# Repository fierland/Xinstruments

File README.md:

NOT DONE YET

This is the code library for my Cessna 172 Cockpit project. Just starting will add the print layouts, sketchuo and other files later. I'm just stating :-)

DONE:
 - design small instruments
 - lasercutter files small instruments
 - electronics small instruments
 - generic code for instruments
 
TODO:
 - big instruments
 - communication (CAN Areospace) layer
 - central controler
 
---

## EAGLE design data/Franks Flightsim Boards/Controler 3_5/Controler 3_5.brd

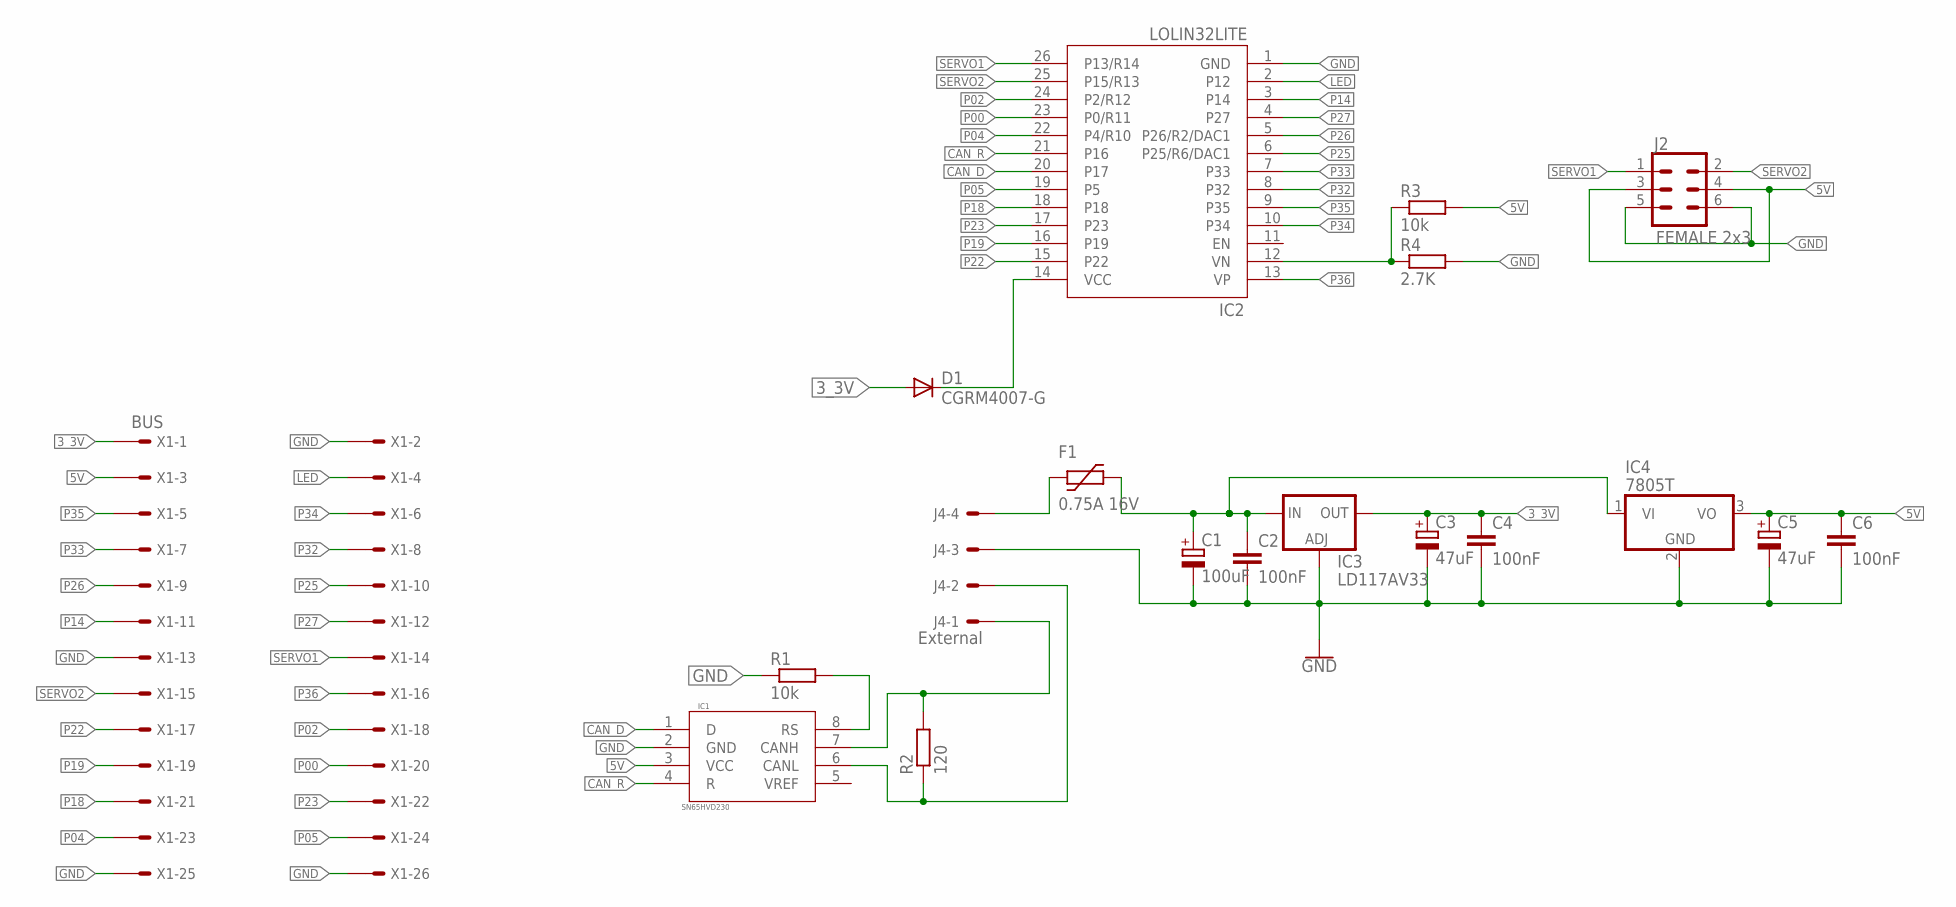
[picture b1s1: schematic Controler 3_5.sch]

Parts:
C1: 100uF; 153CLV-0505
C2, C4, C6: 100nF; C0805
C3, C5: 47uF; CT3528
D1: CGRM4007-G; SOD-123_MINI-SMA
F1: 0.75A 16V; 1812L
IC1: SN65HVD230; SO08
IC2: LOLIN32LITE
IC3: LD117AV33; TO220L1
IC4: 7805T; TO220H
J2: FEMALE 2x3; 2X3
J4: External; 6410-04
R1, R3: 10k; M1206
R2: 120; R1210
R4: 2.7K; M1206
X1: BUS; 057-026-1

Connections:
3_3V: C3.+, C4.1, D1.A, IC3.2 (OUT), X1.1
5V: C5.+, C6.1, IC1.3 (VCC), IC4.3 (VO), J2.3, J2.4, R3.2, X1.3
12V: C1.+, C2.1, F1.2, IC3.3 (IN), IC4.1 (VI)
CAN_D: IC1.1 (D), IC2.20 (P17)
CAN_R: IC1.4 (R), IC2.21 (P16)
GND: C1.-, C2.2, C3.-, C4.2, C5.-, C6.2, IC1.2 (GND), IC2.1 (GND), IC3.1 (ADJ), IC4.2 (GND), J2.5, J2.6, J4.3, R1.1, R4.2, X1.2, X1.13, X1.25, X1.26
LED: IC2.2 (P12), X1.4
unnamed: IC1.8 (RS), R1.2
unnamed: IC1.7 (CANH), J4.1, R2.2
unnamed: IC1.6 (CANL), J4.2, R2.1
unnamed: F1.1, J4.4
unnamed: D1.C, IC2.14 (VCC)
P00: IC2.23 (P0/R11), X1.20
P02: IC2.24 (P2/R12), X1.18
P04: IC2.22 (P4/R10), X1.23
P05: IC2.19 (P5), X1.24
P14: IC2.3 (P14), X1.11
P18: IC2.18, X1.21
P19: IC2.16 (P19), X1.19
P22: IC2.15 (P22), X1.17
P23: IC2.17 (P23), X1.22
P25: IC2.6 (P25/R6/DAC1), X1.10
P26: IC2.5 (P26/R2/DAC1), X1.9
P27: IC2.4 (P27), X1.12
P32: IC2.8 (P32), X1.8
P33: IC2.7 (P33), X1.7
P34: IC2.10 (P34), X1.6
P35: IC2.9 (P35), X1.5
P36: IC2.13 (VP), X1.16
P39: IC2.12 (VN), R3.1, R4.1
SERVO1: IC2.26 (P13/R14), J2.1, X1.14
SERVO2: IC2.25 (P15/R13), J2.2, X1.15

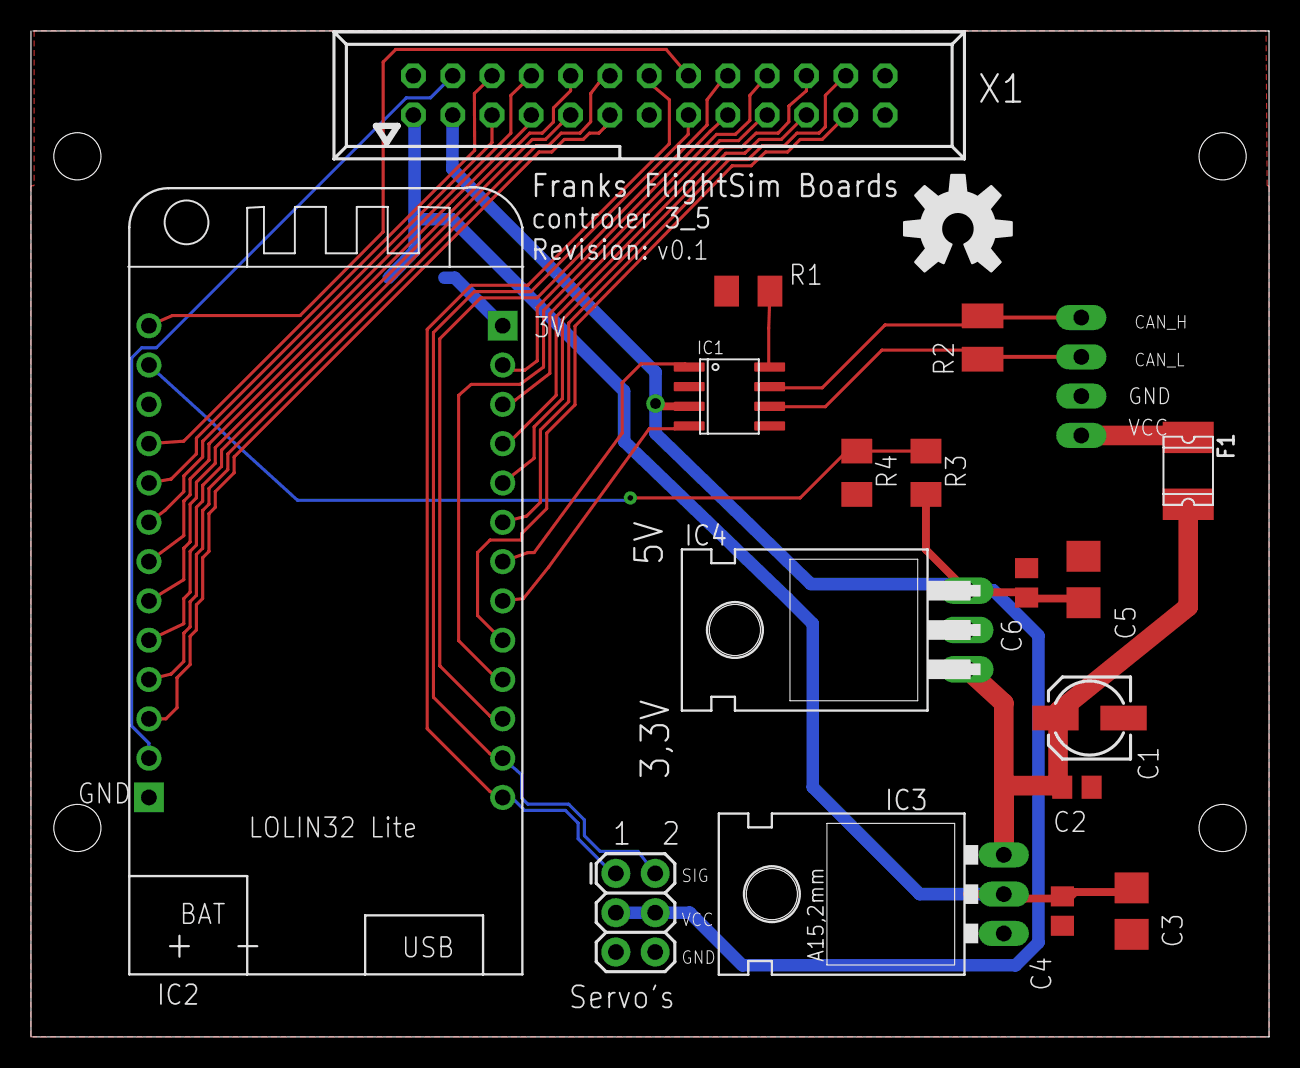
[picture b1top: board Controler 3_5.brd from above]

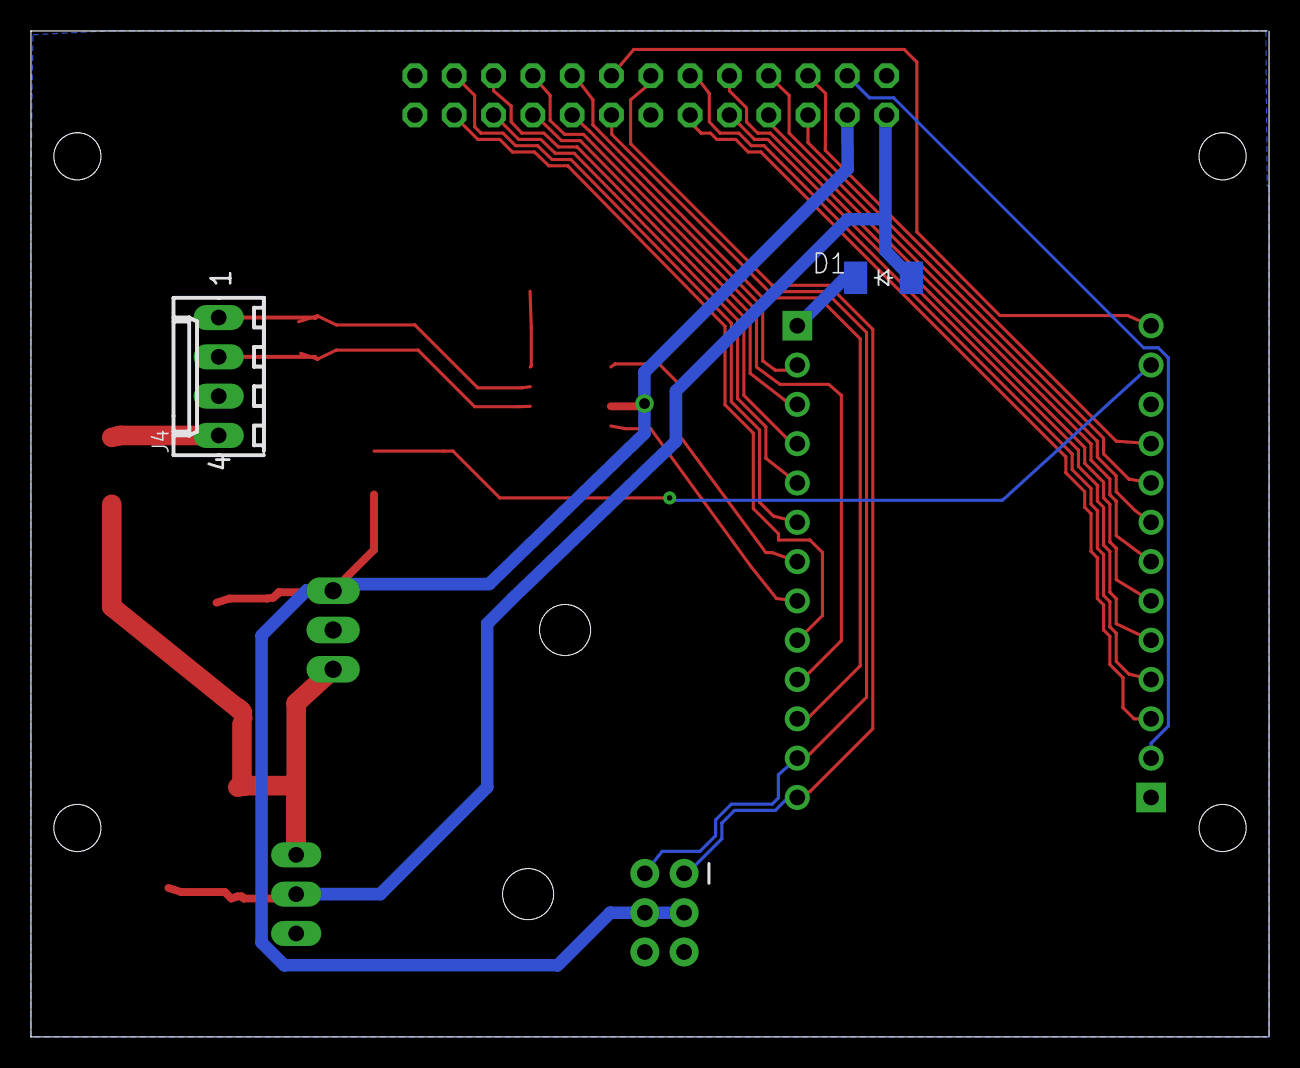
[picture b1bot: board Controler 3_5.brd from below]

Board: 2 copper layers, 80.0 x 65.0 mm, 24 parts (2 on the bottom side), 32 nets.

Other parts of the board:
U$10: OSHW-LOGO-L
U$13, U$14, U$15, U$16: STAND-OFF-TIGHT

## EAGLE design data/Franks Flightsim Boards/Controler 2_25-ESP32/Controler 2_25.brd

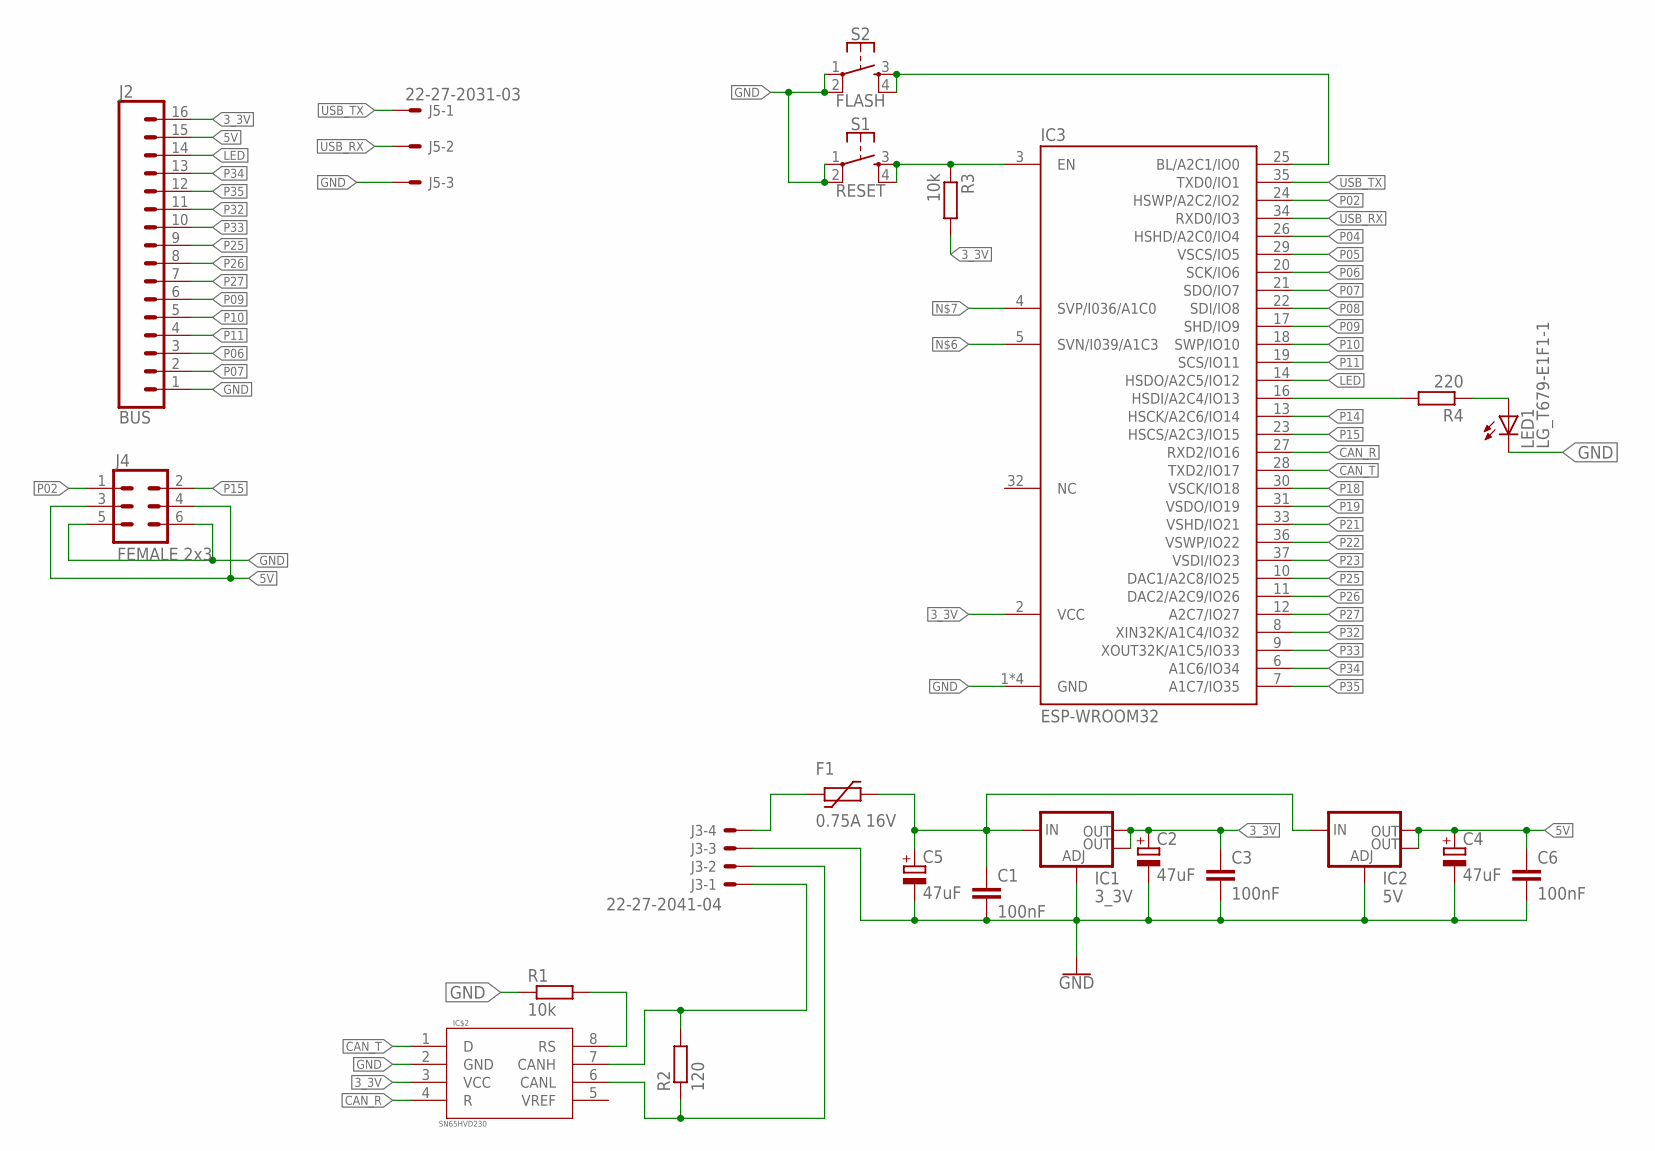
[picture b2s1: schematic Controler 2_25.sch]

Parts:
C1, C3, C6: 100nF; C1206
C2, C4: 47uF; CT3528
C5: 47uF; 153CLV-0605
F1: 0.75A 16V; 1812L
IC1: 3_3V; SOT223
IC2: 5V; SOT223
IC3: ESP-WROOM32
IC$2: SN65HVD230; SO08
J2: BUS; 1X16
J3: 22-27-2041-04; 6410-04
J4: FEMALE 2x3; 2X3
J5: 22-27-2031-03; 6410-03
LED1: LG_T679-E1F1-1; PLCC2
R1, R3: 10k; M1206
R2: 120; R1210
R4: 220; M1206
S1: RESET; TACTILE_SWITCH_SMD_4.6X2.8MM
S2: FLASH; TACTILE_SWITCH_SMD_4.6X2.8MM

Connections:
3_3V: C2.- (+), C3.1, IC1.2 (OUT), IC1.4 (OUT), IC3.2 (VCC), IC$2.3 (VCC), J2.16, R3.2
5V: C4.- (+), C6.1, IC2.2 (OUT), IC2.4 (OUT), J2.15, J4.3, J4.4
12V: C1.1, C5.+, F1.2, IC1.3 (IN), IC2.3 (IN)
CAN_R: IC3.27 (RXD2/IO16), IC$2.4 (R)
CAN_T: IC3.28 (TXD2/IO17), IC$2.1 (D)
GND: C1.2, C2.+ (-), C3.2, C4.+ (-), C5.-, C6.2, IC1.1 (ADJ), IC2.1 (ADJ), IC3.1 (GND), IC3.15 (GND), IC3.38 (GND), IC3.TP (GND), IC$2.2 (GND), J2.1, J3.3, J4.5, J4.6, J5.3, LED1.C, R1.1, S1.1, S1.2, S2.1, S2.2
LED: IC3.14 (HSDO/A2C5/IO12), J2.14
unnamed: IC$2.8 (RS), R1.2
unnamed: IC$2.7 (CANH), J3.1, R2.2
unnamed: IC$2.6 (CANL), J3.2, R2.1
unnamed: LED1.A, R4.1
unnamed: F1.1, J3.4
P00: IC3.25 (BL/A2C1/IO0), S2.3, S2.4
P02: IC3.24 (HSWP/A2C2/IO2), J4.1
P04: IC3.26 (HSHD/A2C0/IO4)
P05: IC3.29 (VSCS/IO5)
P06: IC3.20 (SCK/IO6), J2.3
P07: IC3.21 (SDO/IO7), J2.2
P08: IC3.22 (SDI/IO8)
P09: IC3.17 (SHD/IO9), J2.6
P10: IC3.18 (SWP/IO10), J2.5
P11: IC3.19 (SCS/IO11), J2.4
P13: IC3.16 (HSDI/A2C4/IO13), R4.2
P14: IC3.13 (HSCK/A2C6/IO14)
P15: IC3.23 (HSCS/A2C3/IO15), J4.2
P18: IC3.30 (VSCK/IO18)
P19: IC3.31 (VSDO/IO19)
P21: IC3.33 (VSHD/IO21)
P22: IC3.36 (VSWP/IO22)
P23: IC3.37 (VSDI/IO23)
P25: IC3.10 (DAC1/A2C8/IO25), J2.9
P26: IC3.11 (DAC2/A2C9/IO26), J2.8
P27: IC3.12 (A2C7/IO27), J2.7
P32: IC3.8 (XIN32K/A1C4/IO32), J2.11
P33: IC3.9 (XOUT32K/A1C5/IO33), J2.10
P34: IC3.6 (A1C6/IO34), J2.13
P35: IC3.7 (A1C7/IO35), J2.12
RESET: IC3.3 (EN), R3.1, S1.3, S1.4
USB_RX: IC3.34 (RXD0/IO3), J5.2
USB_TX: IC3.35 (TXD0/IO1), J5.1

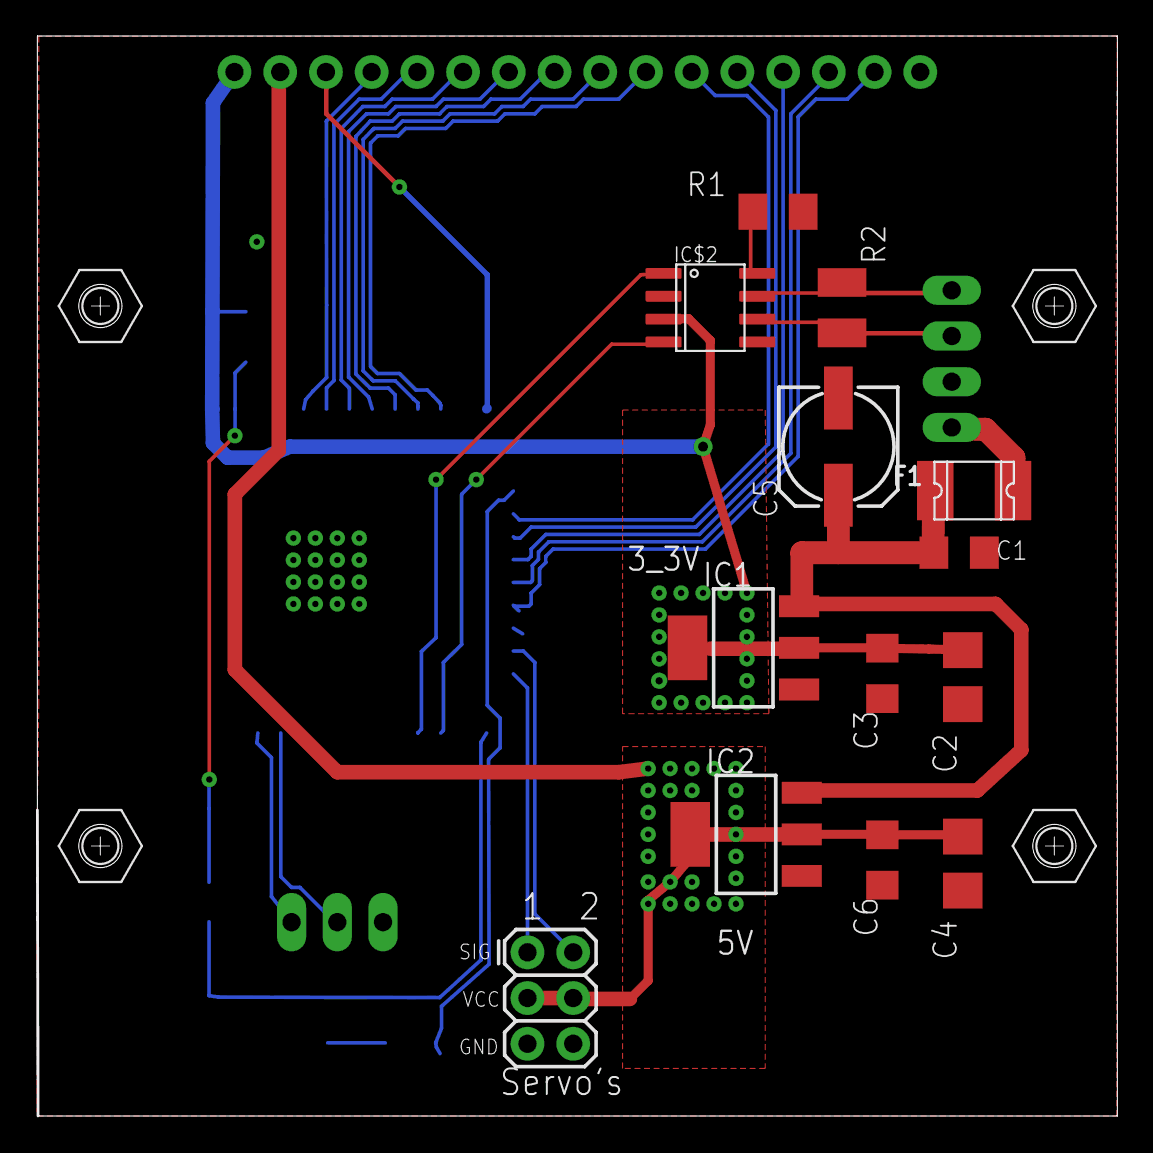
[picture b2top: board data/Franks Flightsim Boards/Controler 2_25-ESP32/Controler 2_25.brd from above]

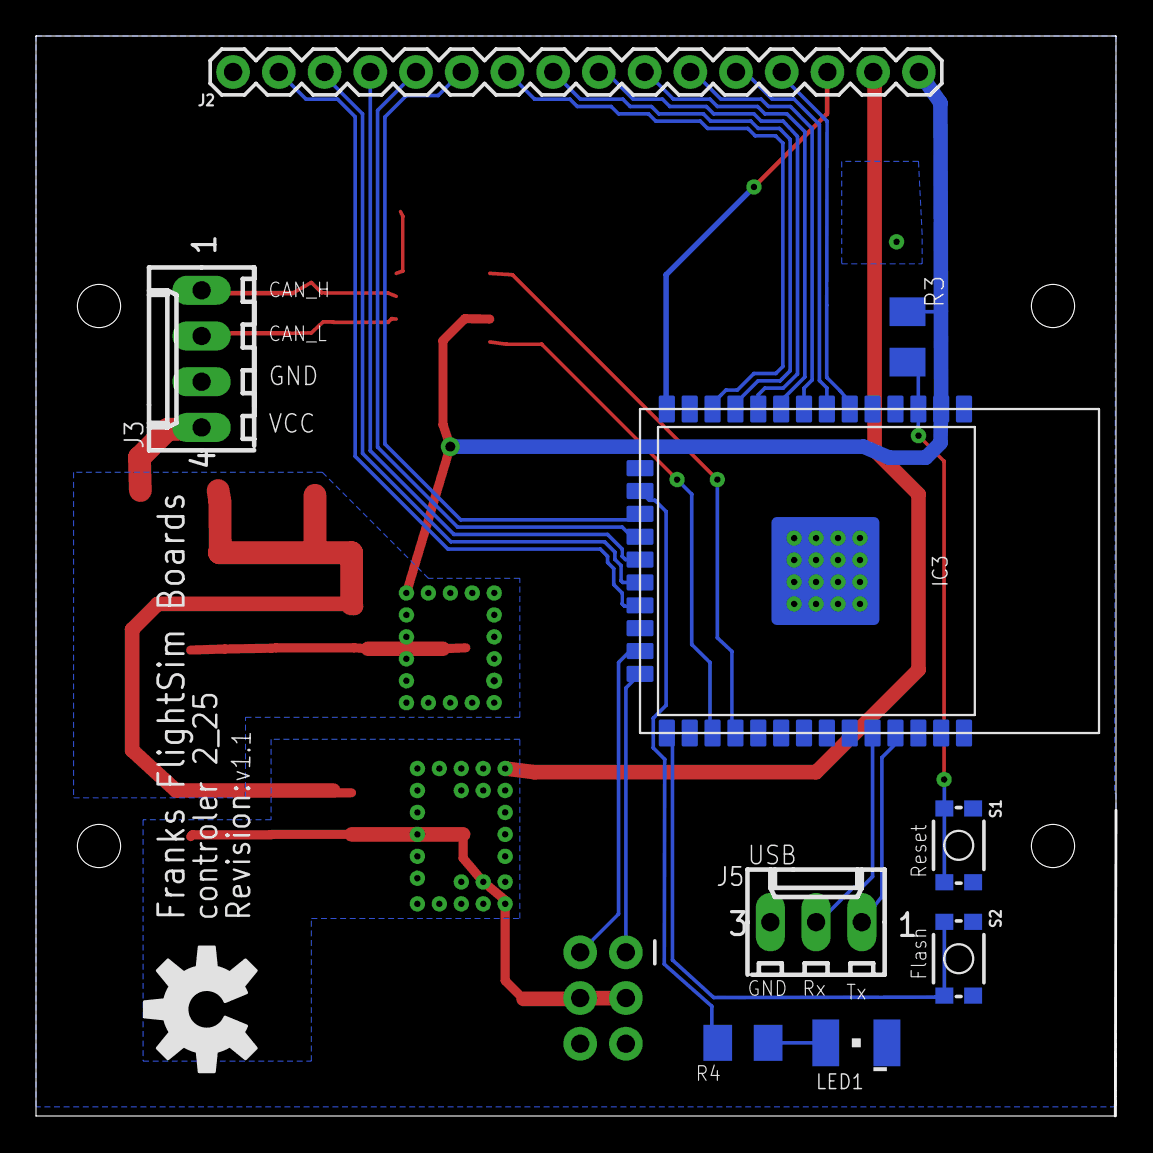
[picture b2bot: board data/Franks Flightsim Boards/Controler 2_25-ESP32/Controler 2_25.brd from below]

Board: 2 copper layers, 59.9 x 59.9 mm, 27 parts (10 on the bottom side), 31 nets.

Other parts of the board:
U$1, U$2, U$3, U$4: M2.0_SW4.0_HOLE
U$10: OSHW-LOGO-L

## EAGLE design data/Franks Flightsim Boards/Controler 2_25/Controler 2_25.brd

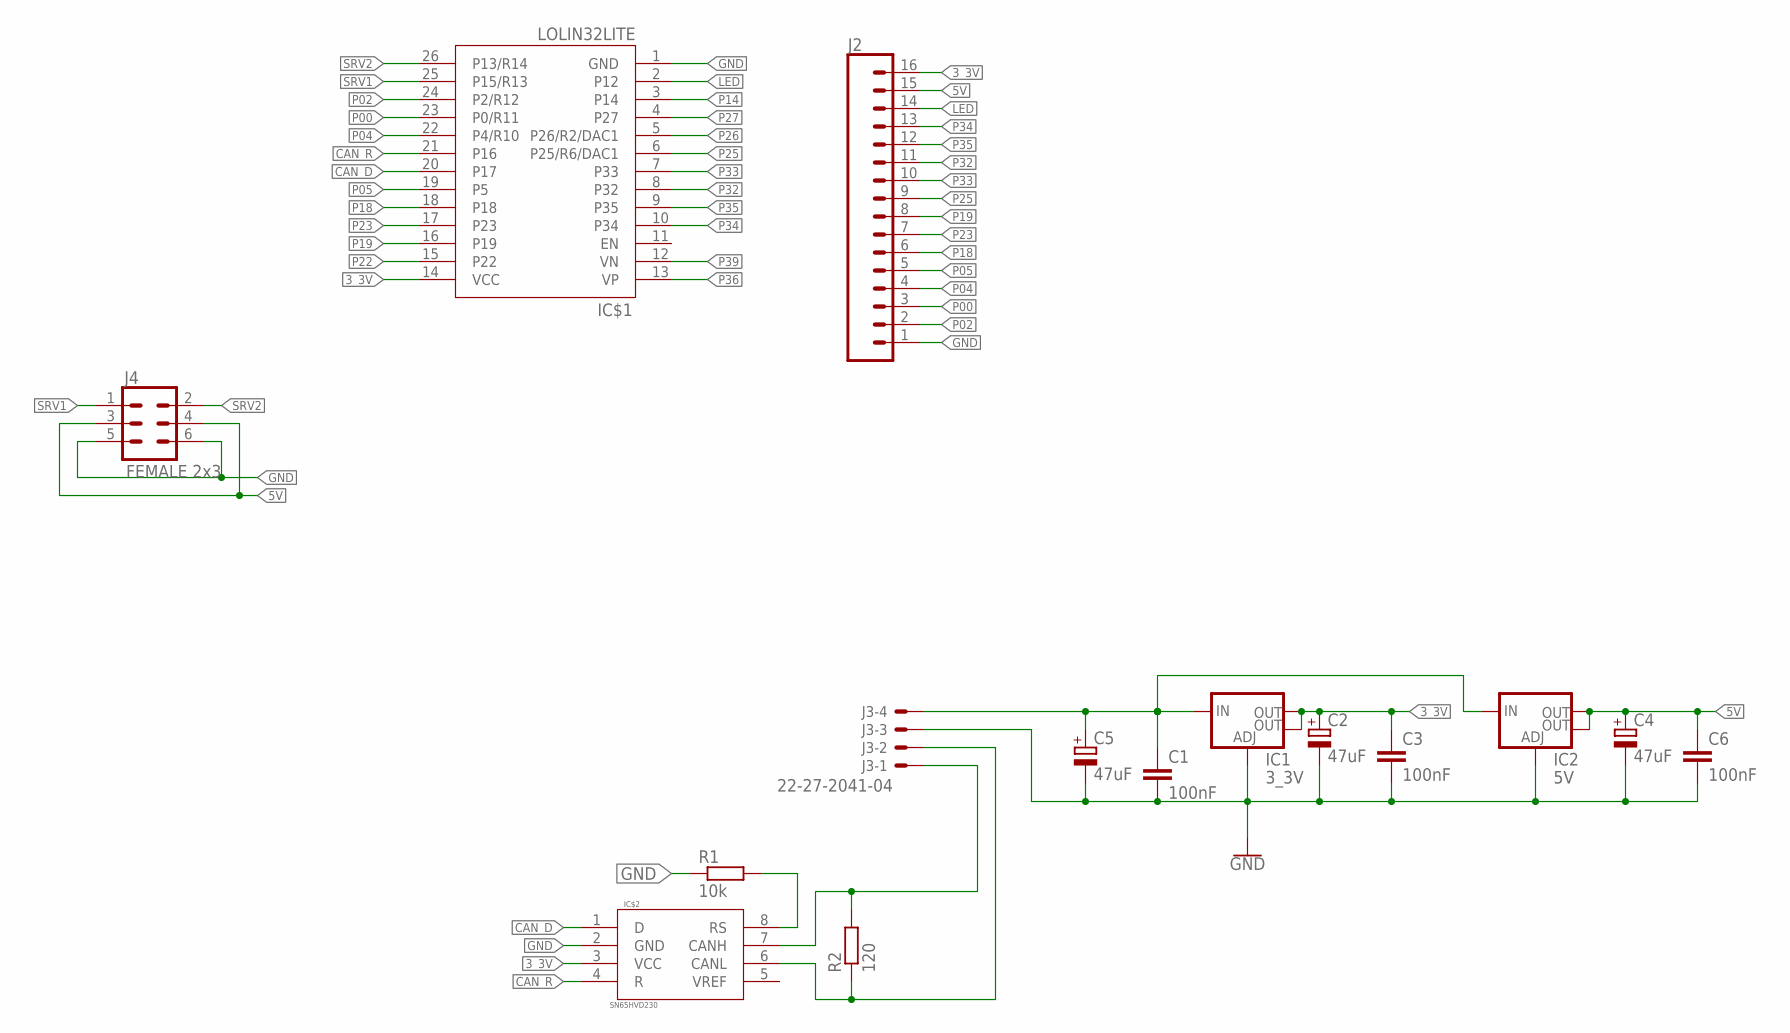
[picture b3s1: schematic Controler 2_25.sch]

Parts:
C1, C3, C6: 100nF; C1206
C2, C4: 47uF; CT3528
C5: 47uF; 153CLV-0605
IC1: 3_3V; SOT223
IC2: 5V; SOT223
IC$1: LOLIN32LITE
IC$2: SN65HVD230; SO08
J2: CONN_16; 1X16
J3: 22-27-2041-04; 6410-04
J4: FEMALE 2x3; 2X3
R1: 10k; M1206
R2: 120; R1210

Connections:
3_3V: C2.- (+), C3.1, IC1.2 (OUT), IC1.4 (OUT), IC$1.14 (VCC), IC$2.3 (VCC), J2.16
5V: C4.- (+), C6.1, IC2.2 (OUT), IC2.4 (OUT), J2.15, J4.3, J4.4
12V: C1.1, C5.+, IC1.3 (IN), IC2.3 (IN), J3.4
CAN_D: IC$1.20 (P17), IC$2.1 (D)
CAN_R: IC$1.21 (P16), IC$2.4 (R)
GND: C1.2, C2.+ (-), C3.2, C4.+ (-), C5.-, C6.2, IC1.1 (ADJ), IC2.1 (ADJ), IC$1.1 (GND), IC$2.2 (GND), J2.1, J3.3, J4.5, J4.6, R1.1
LED: IC$1.2 (P12), J2.14
unnamed: IC$2.8 (RS), R1.2
unnamed: IC$2.7 (CANH), J3.1, R2.2
unnamed: IC$2.6 (CANL), J3.2, R2.1
P00: IC$1.23 (P0/R11), J2.3
P02: IC$1.24 (P2/R12), J2.2
P04: IC$1.22 (P4/R10), J2.4
P05: IC$1.19 (P5), J2.5
P14: IC$1.3 (P14)
P18: IC$1.18, J2.6
P19: IC$1.16 (P19), J2.8
P22: IC$1.15 (P22)
P23: IC$1.17 (P23), J2.7
P25: IC$1.6 (P25/R6/DAC1), J2.9
P26: IC$1.5 (P26/R2/DAC1)
P27: IC$1.4 (P27)
P32: IC$1.8 (P32), J2.11
P33: IC$1.7 (P33), J2.10
P34: IC$1.10 (P34), J2.13
P35: IC$1.9 (P35), J2.12
P36: IC$1.13 (VP)
P39: IC$1.12 (VN)
SRV1: IC$1.25 (P15/R13), J4.1
SRV2: IC$1.26 (P13/R14), J4.2

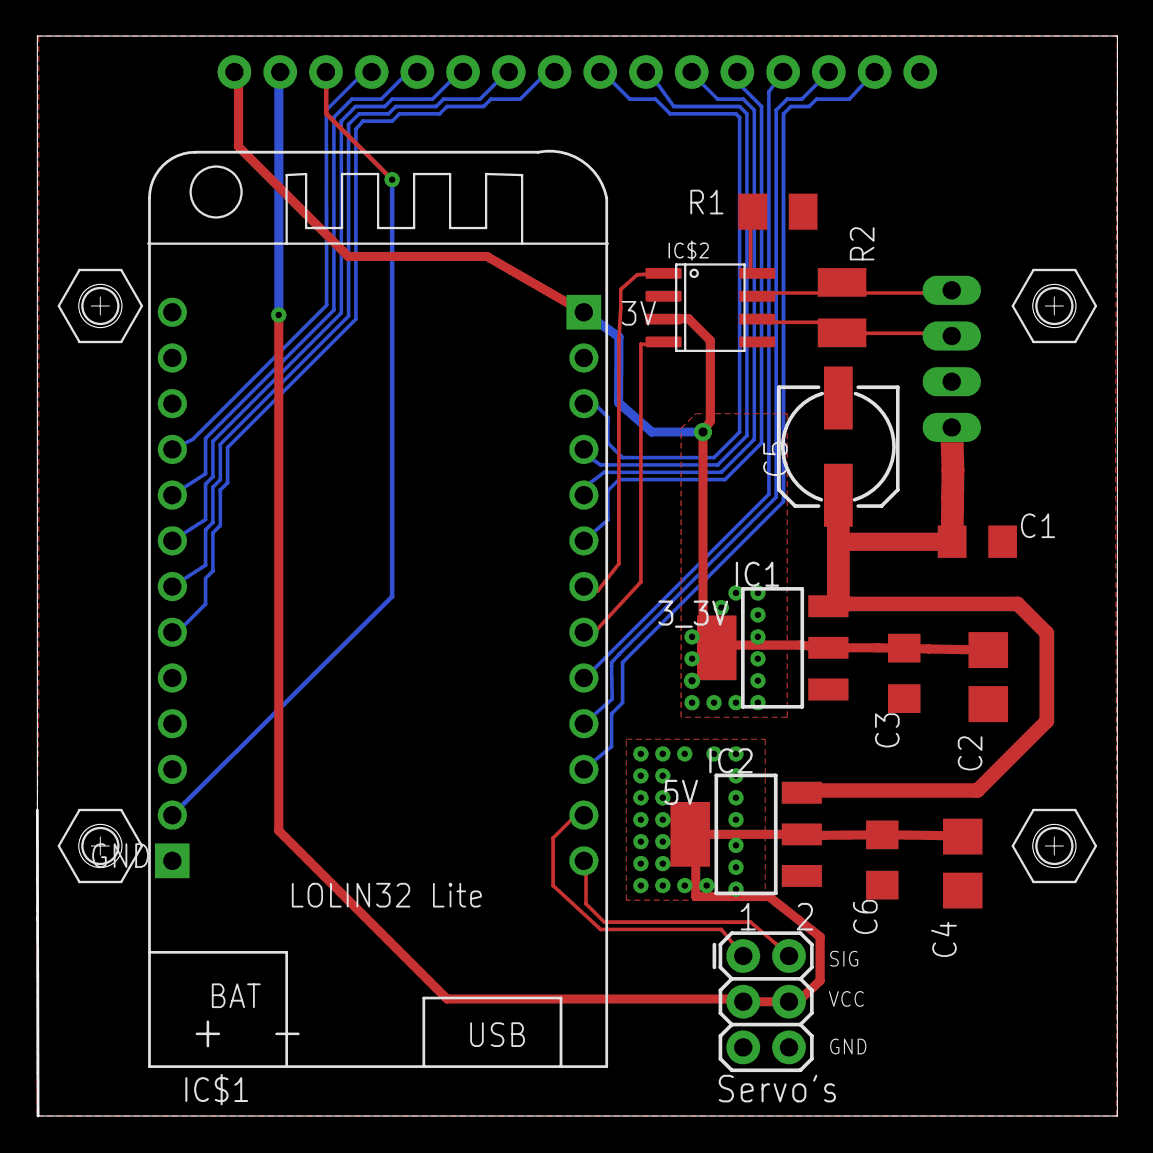
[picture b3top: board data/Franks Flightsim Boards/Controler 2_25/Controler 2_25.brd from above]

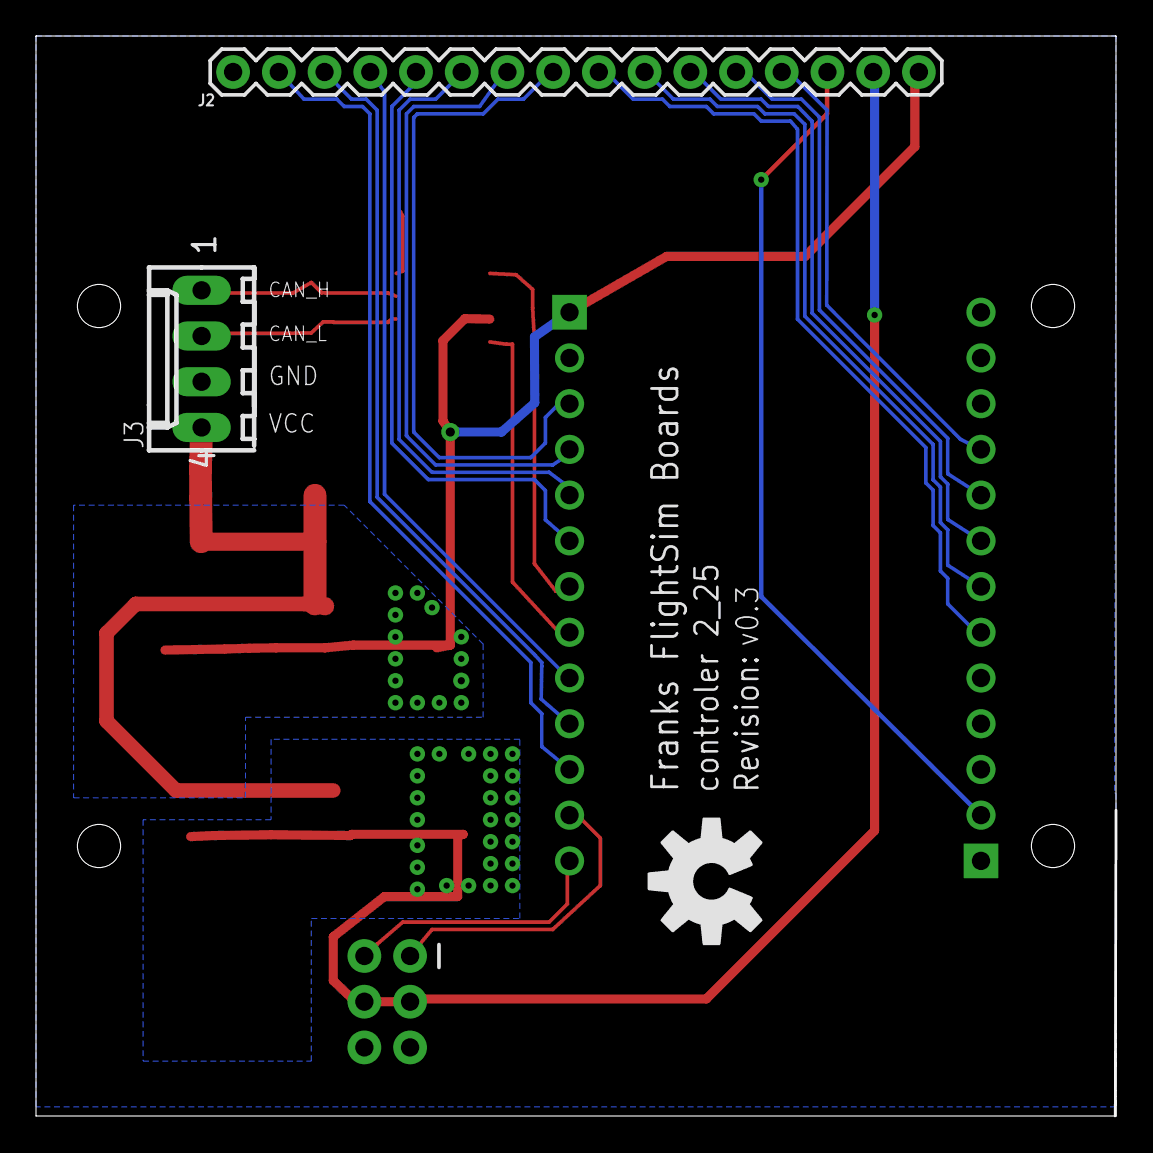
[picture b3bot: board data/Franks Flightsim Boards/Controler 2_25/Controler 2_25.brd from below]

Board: 2 copper layers, 59.9 x 59.9 mm, 20 parts (3 on the bottom side), 24 nets.

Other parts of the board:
U$1, U$2, U$3, U$4: M2.0_SW4.0_HOLE
U$10: OSHW-LOGO-L

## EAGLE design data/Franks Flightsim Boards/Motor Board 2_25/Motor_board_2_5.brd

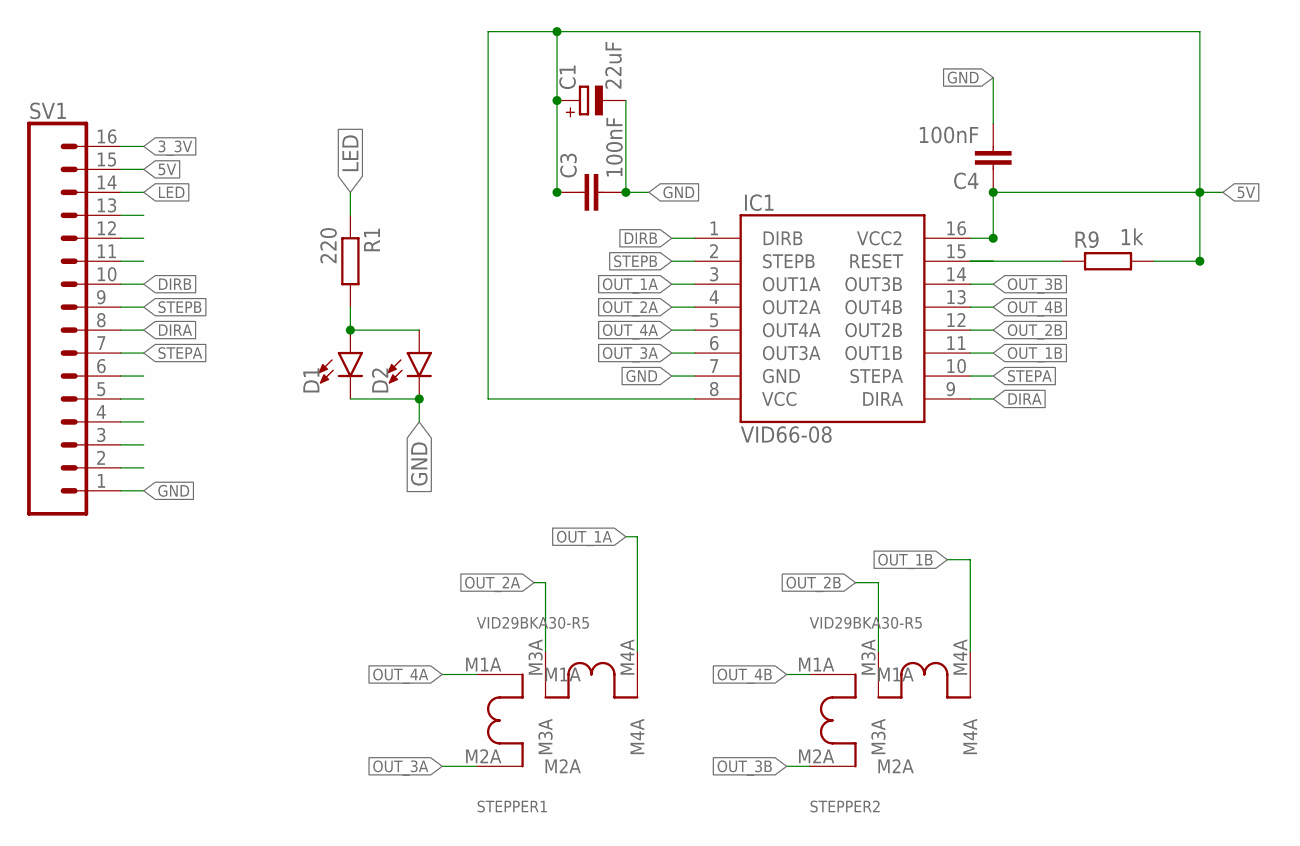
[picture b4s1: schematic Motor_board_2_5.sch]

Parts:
C1: 22uF; 153CLV-0605
C3, C4: 100nF; C1206K
D1, D2: LED-3MM-NO_SILK; LED_3MM-NS
IC1: VID66-08; SO16
R1: 220; 0204/7
R9: 1k; M0805
STEPPER1, STEPPER2: VID29BKA30-R5; BKA30-R5
SV1: CONN_16; 1X16

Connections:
3_3V: SV1.16
5V: C1.+, C3.1, C4.1, IC1.8 (VCC), IC1.16 (VCC2), R9.2, SV1.15
DIRA: IC1.9 (DIRA), SV1.8
DIRB: IC1.1 (DIRB), SV1.10
GND: C1.-, C3.2, C4.2, D1.K (C), D2.K (C), IC1.7 (GND), SV1.1
LED: R1.1, SV1.14
unnamed: D1.A, D2.A, R1.2
unnamed: IC1.15 (RESET), R9.1
OUT_1A: IC1.3 (OUT1A), STEPPER1.M4A
OUT_1B: IC1.11 (OUT1B), STEPPER2.M4A
OUT_2A: IC1.4 (OUT2A), STEPPER1.M3A
OUT_2B: IC1.12 (OUT2B), STEPPER2.M3A
OUT_3A: IC1.6 (OUT3A), STEPPER1.M2A
OUT_3B: IC1.14 (OUT3B), STEPPER2.M2A
OUT_4A: IC1.5 (OUT4A), STEPPER1.M1A
OUT_4B: IC1.13 (OUT4B), STEPPER2.M1A
STEPA: IC1.10 (STEPA), SV1.7
STEPB: IC1.2 (STEPB), SV1.9

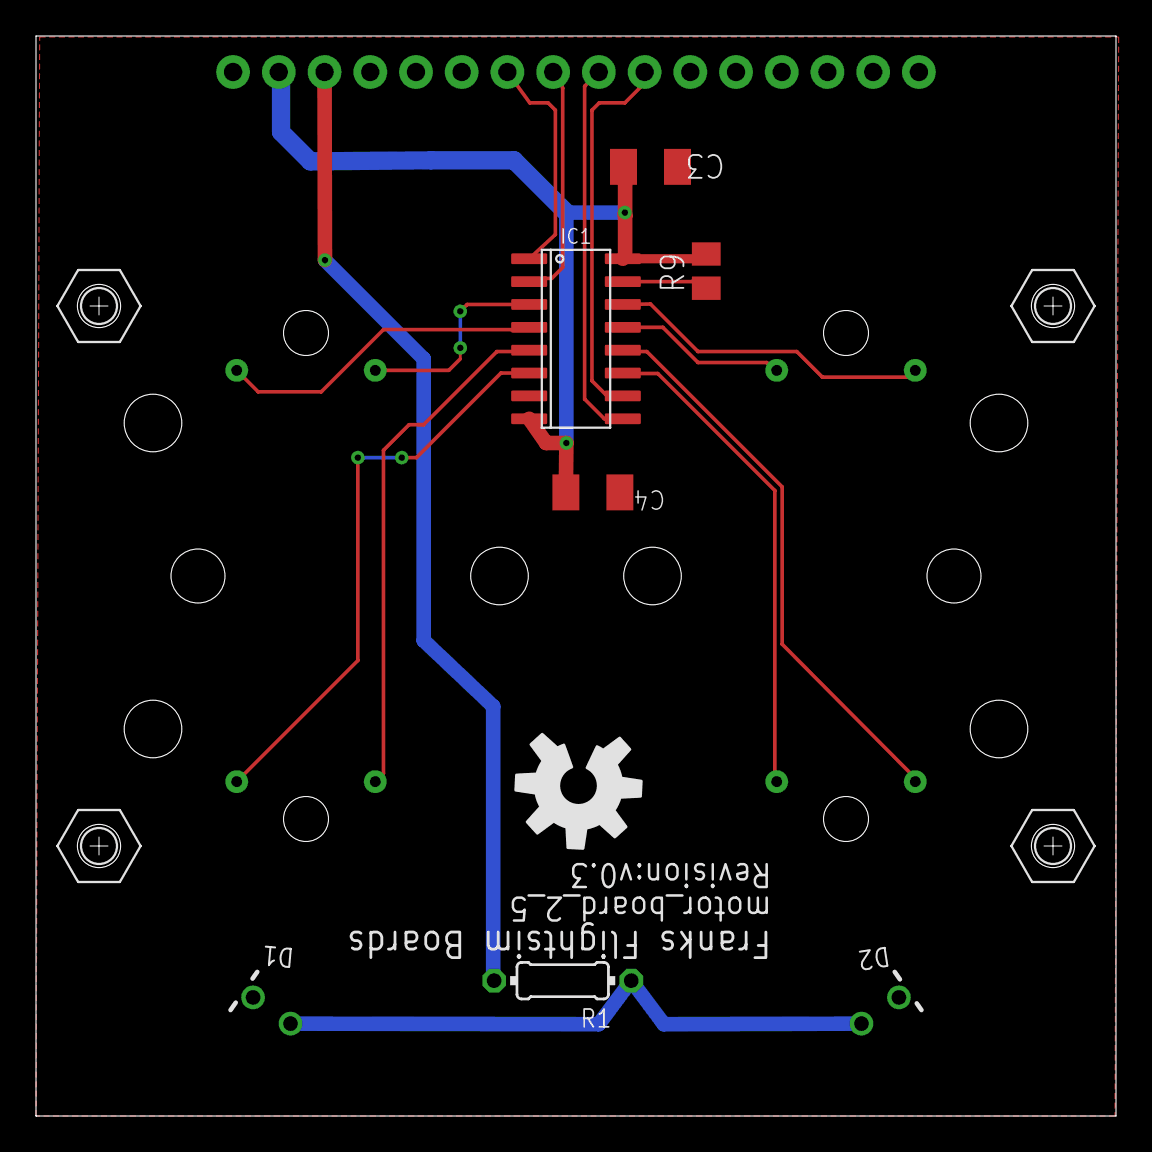
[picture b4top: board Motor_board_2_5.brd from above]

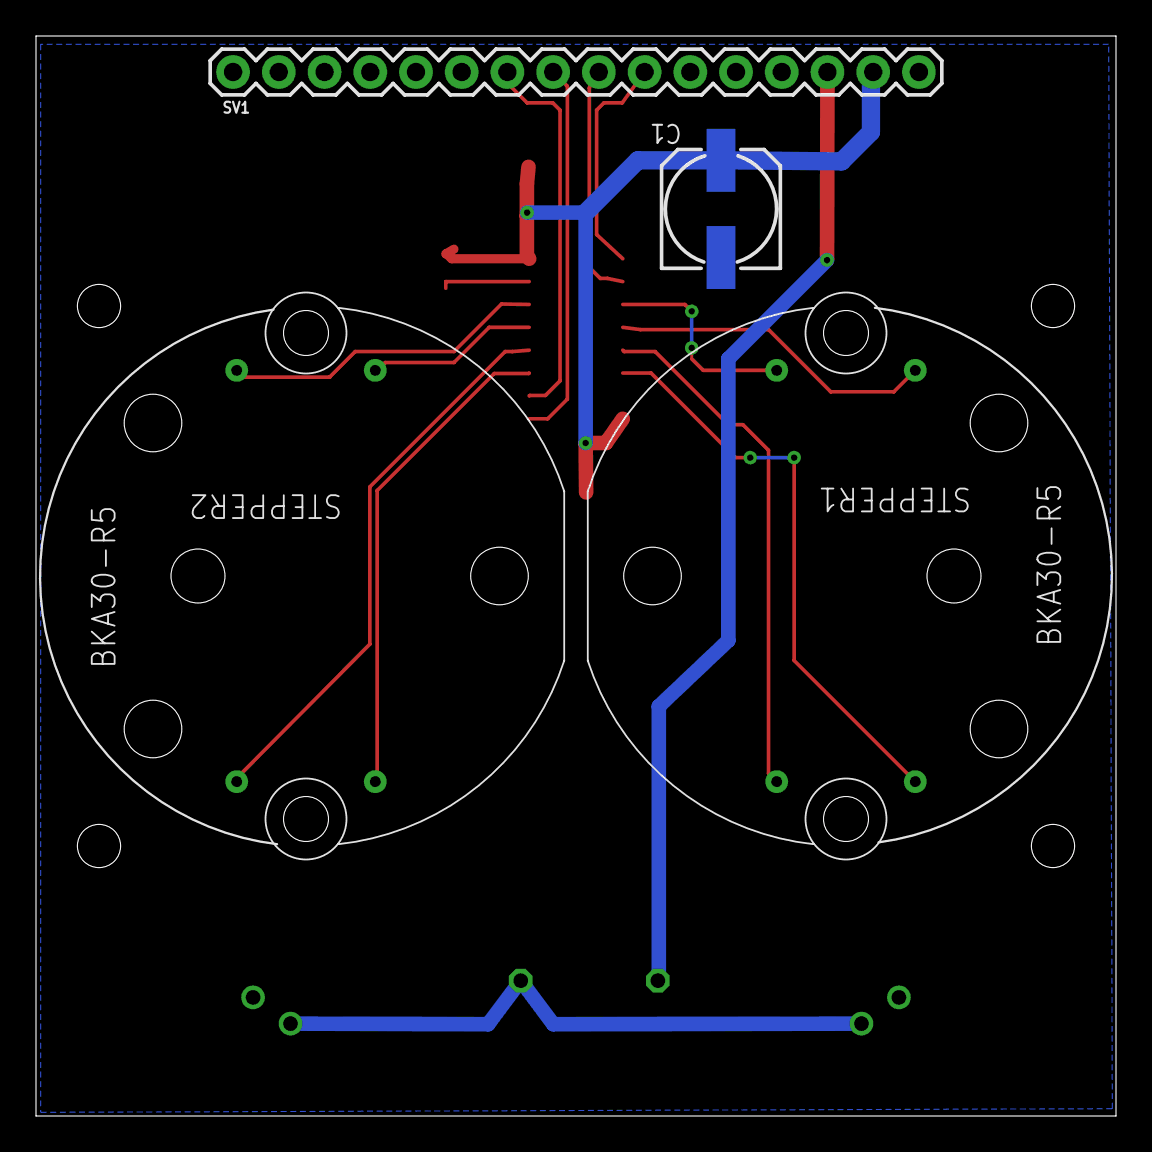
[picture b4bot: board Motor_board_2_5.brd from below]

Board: 2 copper layers, 60.0 x 60.0 mm, 16 parts (4 on the bottom side), 17 nets.

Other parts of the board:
U$1, U$2, U$3, U$4: M2.0_SW4.0_HOLE
U$9: OSHW-LOGO-L

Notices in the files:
parts and their libraries:
SparkFun-Aesthetics: Licensing: Creative Commons ShareAlike 4.0 International - https://creativecommons.org/licenses/by-sa/4.0
